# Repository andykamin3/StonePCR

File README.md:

# StonePCR
*Por Joaquín Alonso, Manuel Agustín Gonzalez y Andrés Kaminker*

## Introducción

### ¿Qué es una máquina de PCR?
También conocido como termociclador es un elemento esencial en laboratorios de biología molecular dado que permite realizar, los ciclos térmicos esenciales en la reacción en cadena de la polimerasa. Es por esto que son utilizados en múltiples procesos, uno de ellos es el test de COVID-19. 
Estos equipos pueden llegar a costar entre 2 y 50 mil dólares en nuestro [país](https://www.onelab.com.ar/pcr). Pese a eso existen alternativas libres como [OpenPCR](https://openpcr.org/) que resultan mucho más baratas. Este es un trabajo que busca ofrecer una alternativa similar a OpenPCR pero con mejores prestaciones a nivel técnico. 

## Selección de Componentes

### ARM Cortex M3

Este microcontrolador fue elegido dado que representaba un improvement por sobre el Atmega328 del OpenPCR. A su vez contaba con pines que soportaban los protocolos necesarios tal como I2C y SPI. Por último contaba con pines que soportaban la interfaz casi directa con un puerto USB, elemento altamente deseable para evitar complicaciones en el desarrollo de la interfaz. Por último, el ADC integrado era suficiente para la lectura de los sensores, proporcionando la precisión suficiente. 
- [Datasheet](https://www.st.com/resource/en/datasheet/stm32f102c8.pdf)
- [Guía de Comienzo Rápido](https://www.st.com/resource/en/application_note/cd00164185-getting-started-with-stm32f10xxx-hardware-development-stmicroelectronics.pdf)

### Comunicación con dispositivos externos

#### USB

En primer lugar dispusimos ofrecer comunicación con una computadora mediante USB-B Micro. De esta manera permitíamos el uso del mismo con un conector fácilmente disponible pero que no agregaba las consideraciones de diseño necesarias del estándar USB-C dado que las prestaciones ofrecidas por este(mayor velocidad y _power delivery_ no fueron consideradas necesarias). Esta interfaz tiene como objetivo ofrecer una configuración rápida y fácil desde la aplicación complementaria en el ordenador. 

#### Bluetooth

Aunque la conexión USB era suficiente, decidimos agregar un módulo Bluetooth (HC-05) que permita la conexión inalámbrica a una app _companion_ en un teléfono celular que facilite el trabajo del usuario y le ofrezca recordatorios y alarmas sin tener que estar permanentemente alerta. 

### Sensado de Temperatura

Para el sensado de temperatura decidimos utilizar termistores NTC ofrecidos por Vishay(Modelo: (NTCLE317E4103SBA [https://www.vishay.com/docs/29216/ntcle317e4103sba.pdf]) que tenían las características técnicas necesarias, especialmente la precisión. A través de un divisor resistivo y el ADC del ARM Cortex M3 obtenemos el valor de temperatura, necesario para realizar correctamente los ciclos térmicos. 

### Placas de Peltier y Drivers

Las placas de Peltier seleccionadas, componente esencial del sistema, fueron un componente complejo de seleccionar pero finalmente nos decantamos por [VT-127-1.0-1.3-71](https://tetech.com/wp-content/uploads/2019/03/VT-127-1.0-1.3-71.pdf) de Tetech. La temperatura soportada y la alta potencia que manejan las convirtieron en una opción idónea para el proceso seleccionado. Los drivers fueron seleccionados en función a las placas de Peltier y sus altos requerimientos eléctricos. Es por eso que el driver [VNH5019A](https://www.pololu.com/product/1449) de Pololu fue seleccionadop porque podía entregar la potencia necesaria y era relativamente asequible. 

### Módulo de Pantalla

Para simplificar el desarrollo de la interfaz de usuario y prescindir de una miríada de botones y perillas decidimos usar una pantalla táctil. Para ello fue seleccionado el módulo de Adafruit [ILI9341](https://www.adafruit.com/product/2478). De esta manera disponemos de una pantalla sin incurrir en complejidades extras.

### Alimentación

Debido a la complejidad que presenta la placa y siguiendo los pasos de OpenPCR nos decantamos por el uso de un conector ATX-24 y una fuente externa lo que facilita el routeo y nos provee de líneas de alimentación con poco ruido en 3.3V y 12V.

## Tareas Pendientes 

- [x] Esquemático
- [x] Placement
- Routeo

## Imágenes

- Render del PCB en 3D

## Instrucciones de Uso del Proyecto
- Realizar una descarga o clonar el repositorio de forma local
- Abrir usando KiCad 5.1.6

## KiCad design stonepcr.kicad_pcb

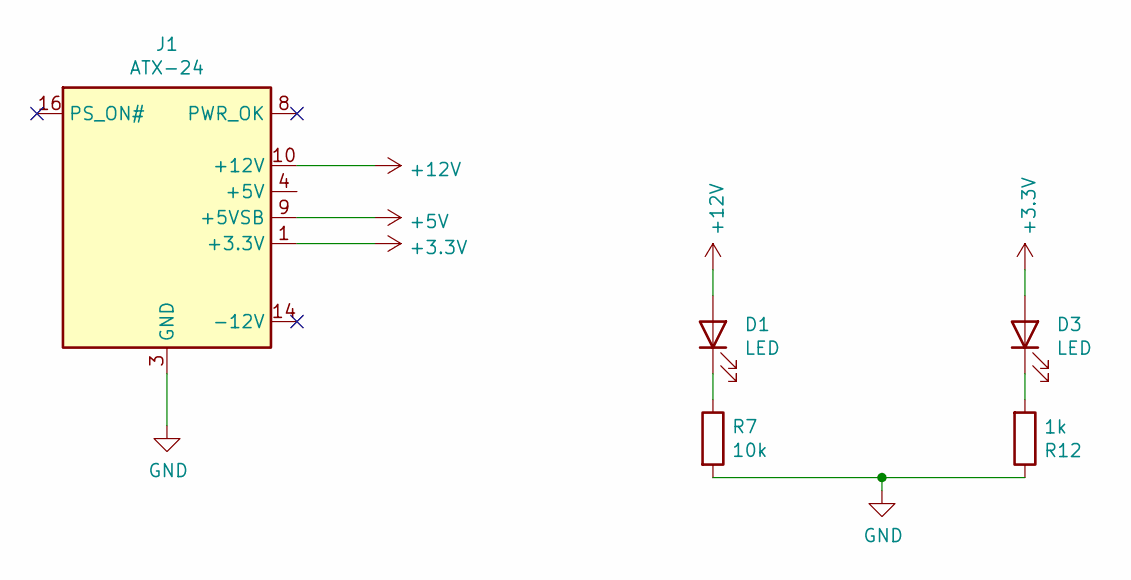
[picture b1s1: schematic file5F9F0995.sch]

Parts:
D1, D3: LED; LED_0805_2012Metric
J1: ATX-24; Molex_Mini-Fit_Jr_5566-24A_2x12_P4.20mm_Vertical
R7: 10k; R_0805_2012Metric
R12: 1k; R_0805_2012Metric

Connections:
+3V3: D3.2 (A), J1.1 (+3.3V), J1.2 (+3.3V), J1.12 (+3.3V), J1.13 (+3.3V); also elsewhere on the board
+5V: J1.9 (+5VSB)
+12V: D1.2 (A), J1.10 (+12V), J1.11 (+12V); also elsewhere on the board
GND: J1.3 (GND), J1.5 (GND), J1.7 (GND), J1.15 (GND), J1.17 (GND), J1.18 (GND), J1.19 (GND), J1.24 (GND), R7.2, R12.1; also elsewhere on the board
unnamed: D1.1 (K), R7.1
unnamed: D3.1 (K), R12.2
unnamed: J1.4 (+5V), J1.6 (+5V), J1.21 (+5V), J1.22 (+5V), J1.23 (+5V)

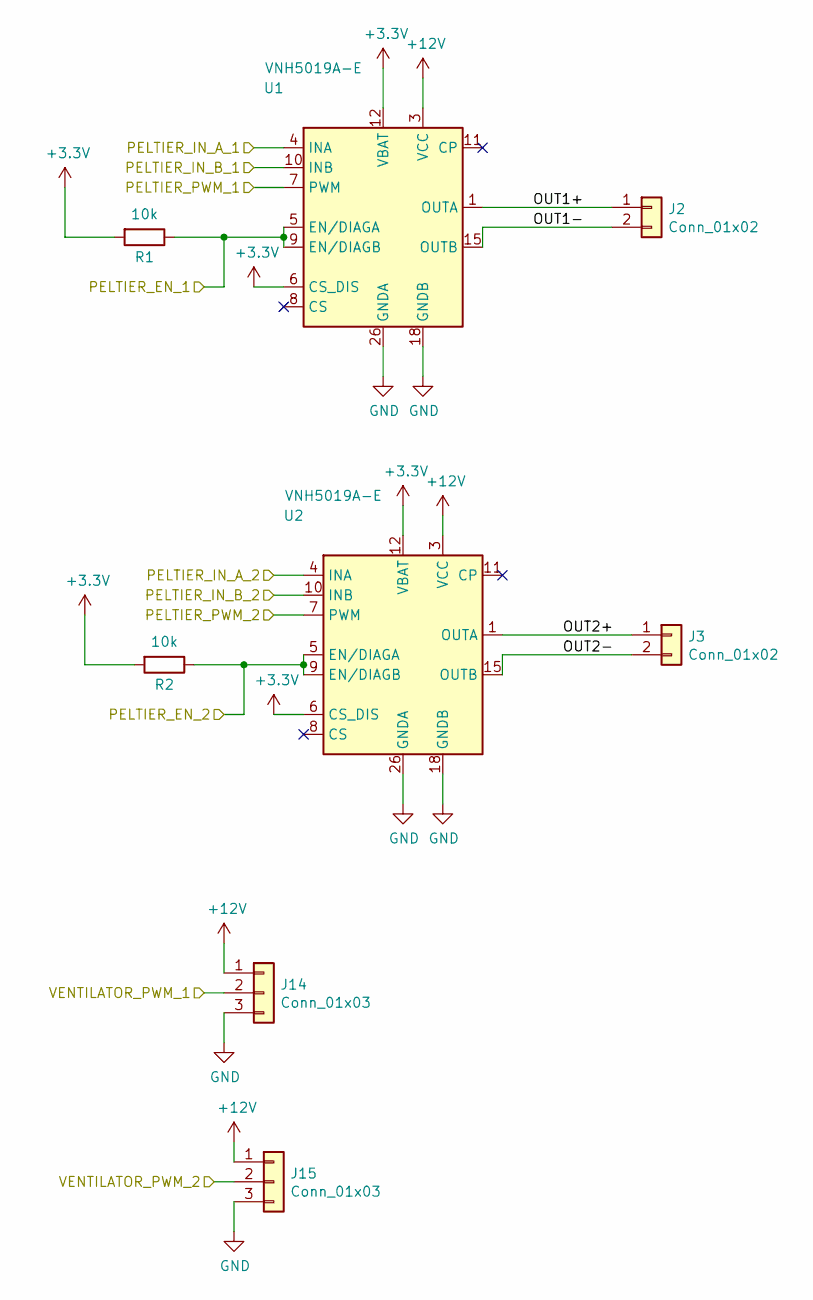
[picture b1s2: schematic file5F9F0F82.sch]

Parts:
J2, J3: Conn_01x02; Molex_Sabre_43160-0102_1x02_P7.49mm_Vertical_ThermalVias
J14, J15: Conn_01x03; PinSocket_1x03_P2.54mm_Vertical
R1, R2: 10k; R_0805_2012Metric
U1, U2: VNH5019A-E; ST_MultiPowerSO-30

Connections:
+3V3: R1.2, R2.2, U1.6 (CS_DIS), U1.12 (VBAT), U2.6 (CS_DIS), U2.12 (VBAT); also elsewhere on the board
+12V: J14.1, J15.1, U1.3 (VCC), U1.13 (VCC), U1.23 (VCC), U1.31 (VCC), U2.3 (VCC), U2.13 (VCC), U2.23 (VCC), U2.31 (VCC); also elsewhere on the board
/ControllerSchematic/PELTIER_EN_1: R1.1, U1.5 (EN/DIAGA), U1.9 (EN/DIAGB); also elsewhere on the board
/ControllerSchematic/PELTIER_EN_2: R2.1, U2.5 (EN/DIAGA), U2.9 (EN/DIAGB); also elsewhere on the board
/ControllerSchematic/PELTIER_IN_A_1: U1.4 (INA); also elsewhere on the board
/ControllerSchematic/PELTIER_IN_A_2: U2.4 (INA); also elsewhere on the board
/ControllerSchematic/PELTIER_IN_B_1: U1.10 (INB); also elsewhere on the board
/ControllerSchematic/PELTIER_IN_B_2: U2.10 (INB); also elsewhere on the board
/ControllerSchematic/PELTIER_PWM_1: U1.7 (PWM); also elsewhere on the board
/ControllerSchematic/PELTIER_PWM_2: U2.7 (PWM); also elsewhere on the board
/ControllerSchematic/VENTILADOR_PWM_1: J15.2; also elsewhere on the board
/ControllerSchematic/VENTILADOR_PWM_2: J14.2; also elsewhere on the board
/PeltierSchematic/OUT1+: J2.1, U1.1 (OUTA), U1.25 (OUTA), U1.30 (OUTA), U1.33 (OUTA)
/PeltierSchematic/OUT1-: J2.2, U1.15 (OUTB), U1.16 (OUTB), U1.21 (OUTB), U1.32 (OUTB)
/PeltierSchematic/OUT2+: J3.1, U2.1 (OUTA), U2.25 (OUTA), U2.30 (OUTA), U2.33 (OUTA)
/PeltierSchematic/OUT2-: J3.2, U2.15 (OUTB), U2.16 (OUTB), U2.21 (OUTB), U2.32 (OUTB)
GND: J14.3, J15.3, U1.18 (GNDB), U1.19 (GNDB), U1.20 (GNDB), U1.26 (GNDA), U1.27 (GNDA), U1.28 (GNDA), U2.18 (GNDB), U2.19 (GNDB), U2.20 (GNDB), U2.26 (GNDA), U2.27 (GNDA), U2.28 (GNDA); also elsewhere on the board

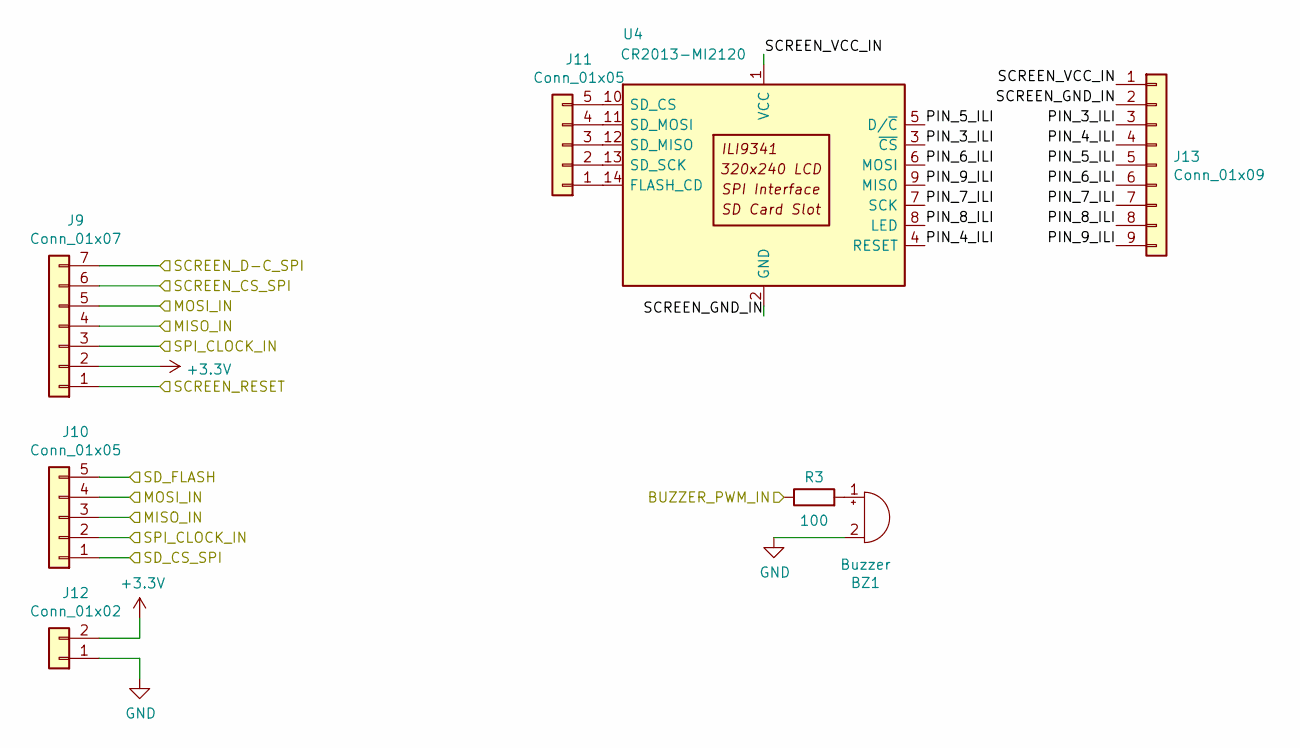
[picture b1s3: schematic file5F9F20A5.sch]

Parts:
BZ1: Buzzer; Buzzer_Mallory_AST1109MLTRQ
J9: Conn_01x07; PinSocket_1x07_P2.54mm_Vertical
J10, J11: Conn_01x05; PinSocket_1x05_P2.54mm_Vertical
J12: Conn_01x02; PinSocket_1x02_P2.54mm_Vertical
J13: Conn_01x09; PinSocket_1x09_P2.54mm_Vertical
R3: 100; R_0805_2012Metric
U4: CR2013-MI2120

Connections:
+3V3: J9.2, J12.2; also elsewhere on the board
/ControllerSchematic/BUZZER_PWM_IN: R3.1; also elsewhere on the board
/ControllerSchematic/SCREEN_CS_SPI: J9.6; also elsewhere on the board
/ControllerSchematic/SCREEN_D-C_SPI: J9.7; also elsewhere on the board
/ControllerSchematic/SCREEN_RESET: J9.1; also elsewhere on the board
/ControllerSchematic/SD_CS_SPI: J10.1; also elsewhere on the board
/ControllerSchematic/SD_FLASH: J10.5; also elsewhere on the board
/ControllerSchematic/SPI_CLOCK_IN: J9.3, J10.2; also elsewhere on the board
/DisplaySchematic/MISO_IN: J9.4, J10.3; also elsewhere on the board
/DisplaySchematic/MOSI_IN: J9.5, J10.4; also elsewhere on the board
/DisplaySchematic/PIN_3_ILI: J13.3, U4.3 (~CS)
/DisplaySchematic/PIN_4_ILI: J13.4, U4.4 (RESET)
/DisplaySchematic/PIN_5_ILI: J13.5, U4.5 (D/~C)
/DisplaySchematic/PIN_6_ILI: J13.6, U4.6 (MOSI)
/DisplaySchematic/PIN_7_ILI: J13.7, U4.7 (SCK)
/DisplaySchematic/PIN_8_ILI: J13.8, U4.8 (LED)
/DisplaySchematic/PIN_9_ILI: J13.9, U4.9 (MISO)
/DisplaySchematic/SCREEN_GND_IN: J13.2, U4.2 (GND)
/DisplaySchematic/SCREEN_VCC_IN: J13.1, U4.1 (VCC)
GND: BZ1.2 (+), J12.1; also elsewhere on the board
unnamed: BZ1.1 (-), R3.2
unnamed: J11.1, U4.14 (FLASH_CD)
unnamed: J11.2, U4.13 (SD_SCK)
unnamed: J11.3, U4.12 (SD_MISO)
unnamed: J11.4, U4.11 (SD_MOSI)
unnamed: J11.5, U4.10 (SD_CS)

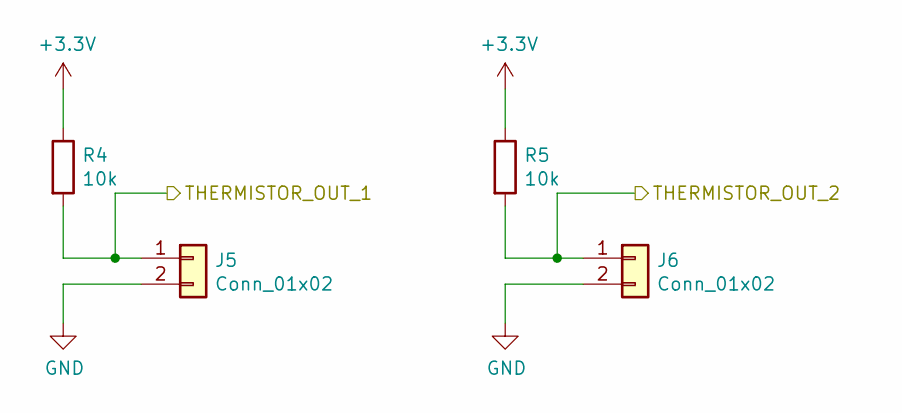
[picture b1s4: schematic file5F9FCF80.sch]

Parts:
J5, J6: Conn_01x02; PinHeader_1x02_P2.54mm_Vertical
R4, R5: 10k; R_0805_2012Metric

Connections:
+3V3: R4.1, R5.1; also elsewhere on the board
/ControllerSchematic/THERMISTOR_IN_1: J5.1, R4.2; also elsewhere on the board
/ControllerSchematic/THERMISTOR_IN_2: J6.1, R5.2; also elsewhere on the board
GND: J5.2, J6.2; also elsewhere on the board

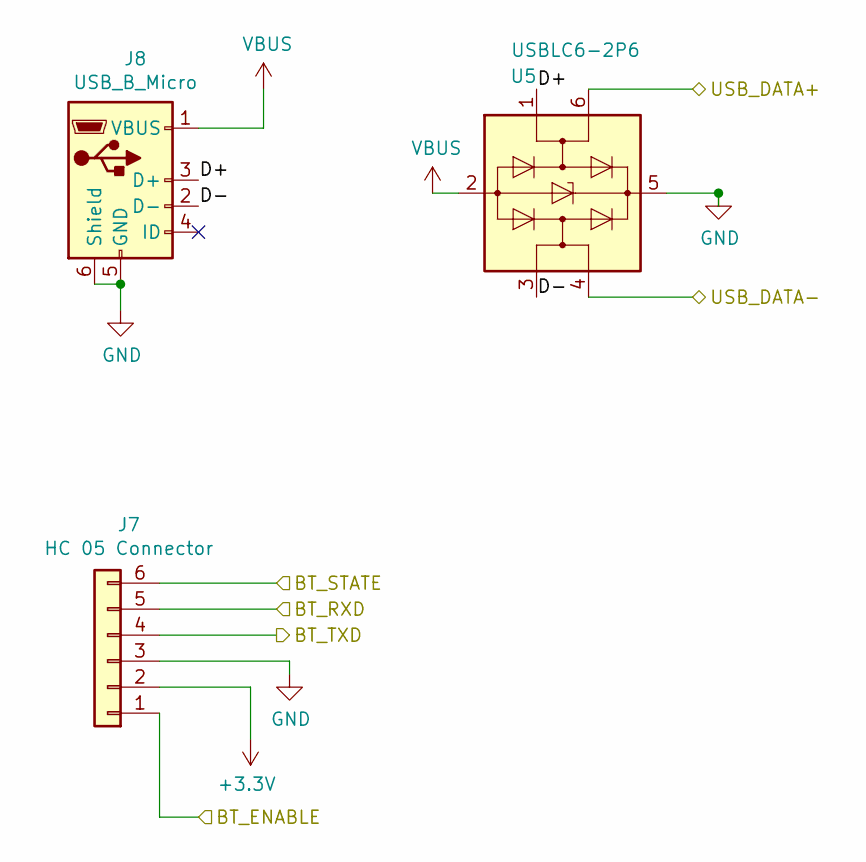
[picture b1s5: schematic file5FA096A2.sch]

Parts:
J7: HC 05 Connector; PinHeader_1x06_P2.54mm_Vertical
J8: USB_B_Micro; USB_Micro-B_Wuerth_629105150521
U5: USBLC6-2P6; SOT-666

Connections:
+3V3: J7.2; also elsewhere on the board
/ControllerSchematic/BT_ENABLE: J7.1; also elsewhere on the board
/ControllerSchematic/BT_RXD: J7.5; also elsewhere on the board
/ControllerSchematic/BT_STATE: J7.6; also elsewhere on the board
/ControllerSchematic/BT_TXD: J7.4; also elsewhere on the board
/ControllerSchematic/USB_DATA+: U5.6 (I/O1); also elsewhere on the board
/ControllerSchematic/USB_DATA-: U5.4 (I/O2); also elsewhere on the board
/InterfacesSchematic/D+: J8.3 (D+), U5.1 (I/O1)
/InterfacesSchematic/D-: J8.2 (D-), U5.3 (I/O2)
GND: J7.3, J8.5 (GND), J8.6 (Shield), U5.5 (VBUS); also elsewhere on the board
VBUS: J8.1 (VBUS), U5.2 (GND)

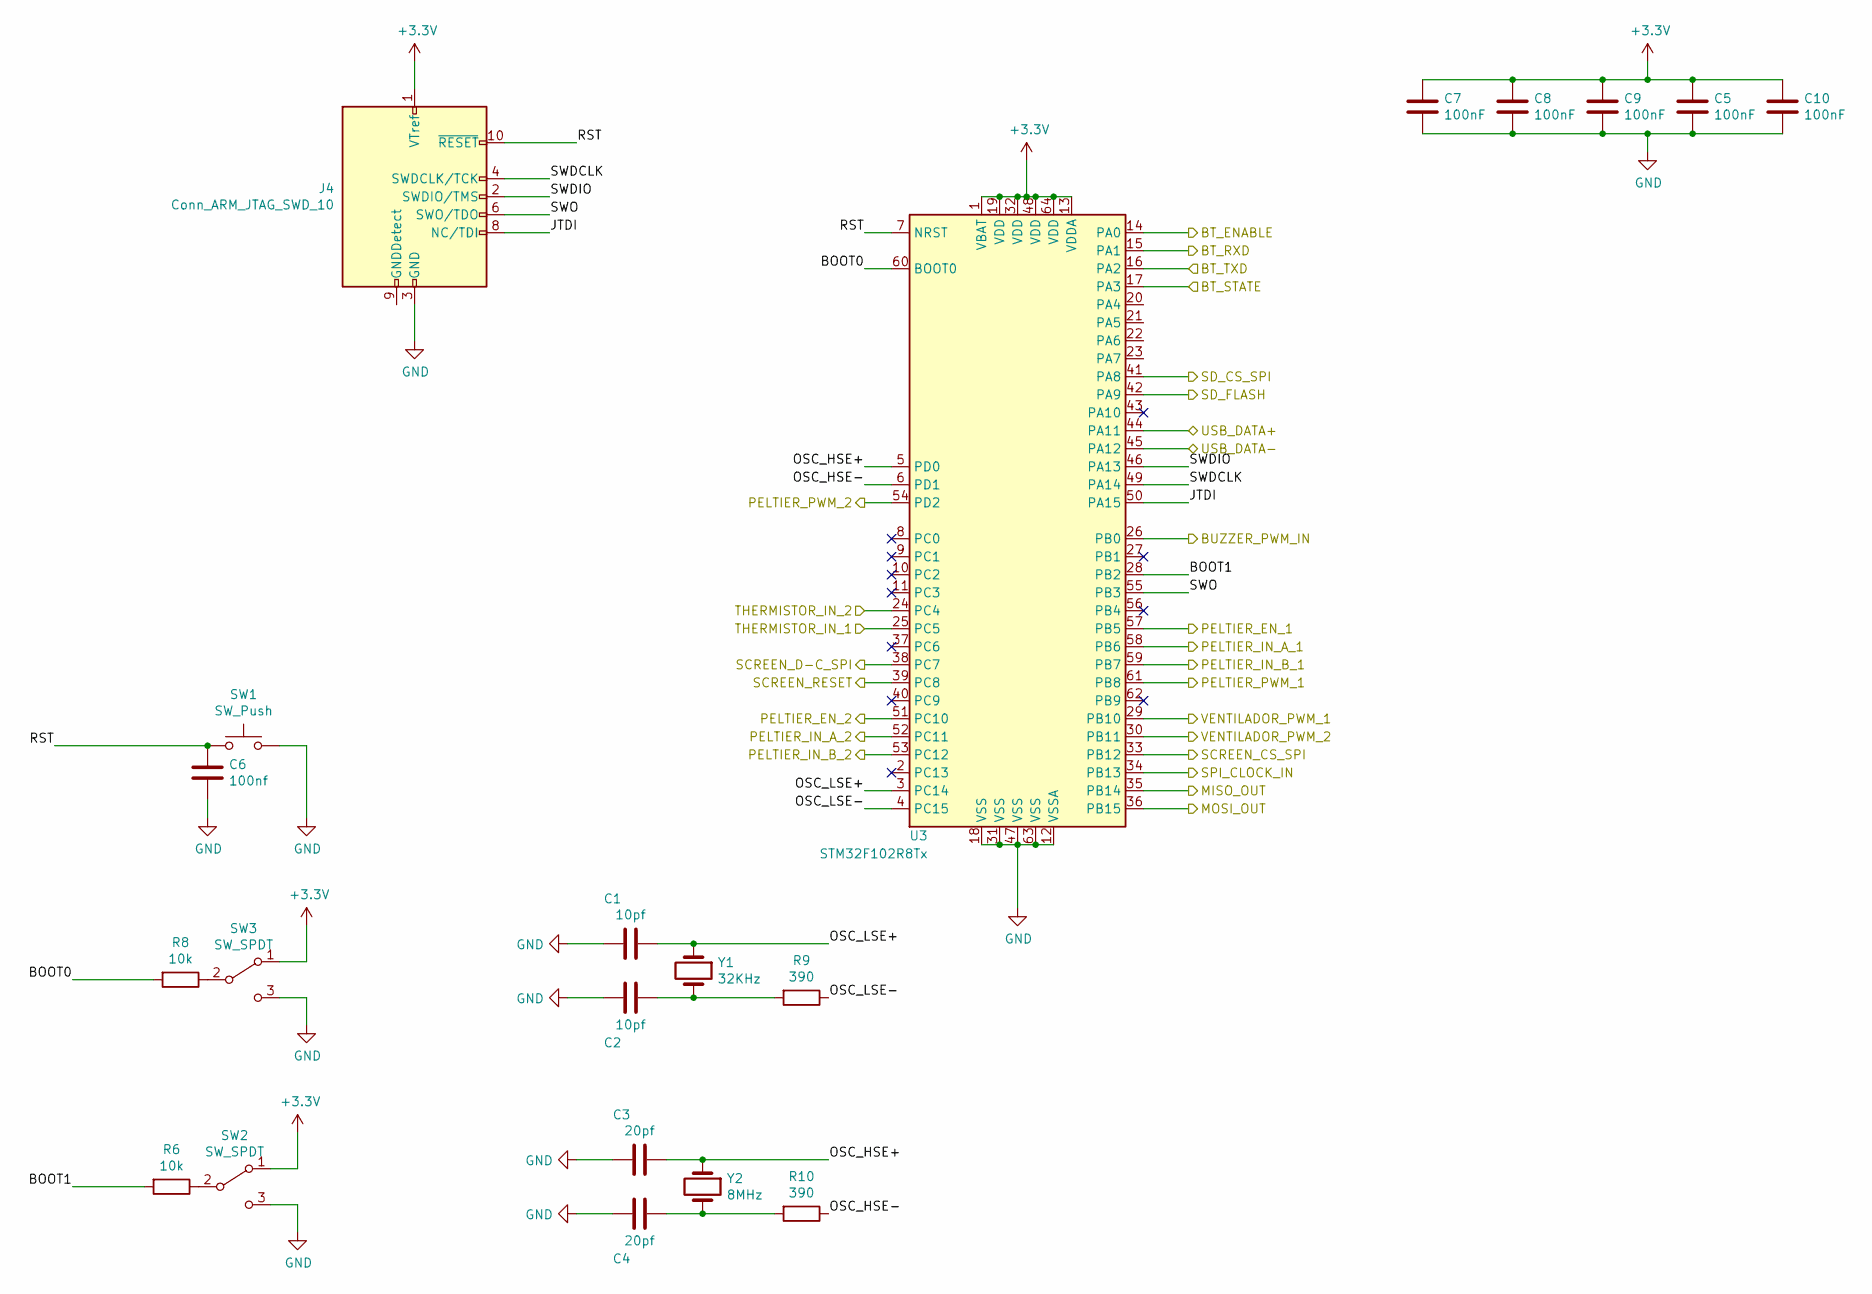
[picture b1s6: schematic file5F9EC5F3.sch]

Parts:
C1, C2: 10pf; C_0805_2012Metric
C3, C4: 20pf; C_0805_2012Metric
C5, C7, C8, C9, C10: 100nF; C_0805_2012Metric
C6: 100nf; C_0805_2012Metric
J4: Conn_ARM_JTAG_SWD_10; JST_EH_B10B-EH-A_1x10_P2.50mm_Vertical
R6, R8: 10k; R_0805_2012Metric
R9, R10: 390; R_0805_2012Metric
SW1: SW_Push; SW_SPST_CK_RS282G05A3
SW2, SW3: SW_SPDT; SW_SPDT_PCM12
U3: STM32F102R8Tx; LQFP-64_10x10mm_P0.5mm
Y1: 32KHz; Resonator-2Pin_W7.0mm_H2.5mm
Y2: 8MHz; Resonator-2Pin_W7.0mm_H2.5mm

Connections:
+3V3: C5.1, C7.1, C8.1, C9.1, C10.1, J4.1 (VTref), SW2.1 (A), SW3.1 (A), U3.1 (VBAT), U3.13 (VDDA), U3.19 (VDD), U3.32 (VDD), U3.48 (VDD), U3.64 (VDD); also elsewhere on the board
/ControllerSchematic/BOOT0: R8.2, U3.60 (BOOT0)
/ControllerSchematic/BOOT1: R6.2, U3.28 (PB2)
/ControllerSchematic/BT_ENABLE: U3.14 (PA0); also elsewhere on the board
/ControllerSchematic/BT_RXD: U3.15 (PA1); also elsewhere on the board
/ControllerSchematic/BT_STATE: U3.17 (PA3); also elsewhere on the board
/ControllerSchematic/BT_TXD: U3.16 (PA2); also elsewhere on the board
/ControllerSchematic/BUZZER_PWM_IN: U3.26 (PB0); also elsewhere on the board
/ControllerSchematic/JTDI: J4.8 (NC/TDI), U3.50 (PA15)
/ControllerSchematic/OSC_HSE+: C3.1, U3.5 (PD0), Y2.1
/ControllerSchematic/OSC_HSE-: R10.1, U3.6 (PD1)
/ControllerSchematic/OSC_LSE+: C1.1, U3.3 (PC14), Y1.1
/ControllerSchematic/OSC_LSE-: R9.1, U3.4 (PC15)
/ControllerSchematic/PELTIER_EN_1: U3.57 (PB5); also elsewhere on the board
/ControllerSchematic/PELTIER_EN_2: U3.51 (PC10); also elsewhere on the board
/ControllerSchematic/PELTIER_IN_A_1: U3.58 (PB6); also elsewhere on the board
/ControllerSchematic/PELTIER_IN_A_2: U3.52 (PC11); also elsewhere on the board
/ControllerSchematic/PELTIER_IN_B_1: U3.59 (PB7); also elsewhere on the board
/ControllerSchematic/PELTIER_IN_B_2: U3.53 (PC12); also elsewhere on the board
/ControllerSchematic/PELTIER_PWM_1: U3.61 (PB8); also elsewhere on the board
/ControllerSchematic/PELTIER_PWM_2: U3.54 (PD2); also elsewhere on the board
/ControllerSchematic/RST: C6.1, J4.10 (~RESET~), SW1.1, U3.7 (NRST)
/ControllerSchematic/SCREEN_CS_SPI: U3.33 (PB12); also elsewhere on the board
/ControllerSchematic/SCREEN_D-C_SPI: U3.38 (PC7); also elsewhere on the board
/ControllerSchematic/SCREEN_RESET: U3.39 (PC8); also elsewhere on the board
/ControllerSchematic/SD_CS_SPI: U3.41 (PA8); also elsewhere on the board
/ControllerSchematic/SD_FLASH: U3.42 (PA9); also elsewhere on the board
/ControllerSchematic/SPI_CLOCK_IN: U3.34 (PB13); also elsewhere on the board
/ControllerSchematic/SWDCLK: J4.4 (SWDCLK/TCK), U3.49 (PA14)
/ControllerSchematic/SWDIO: J4.2 (SWDIO/TMS), U3.46 (PA13)
/ControllerSchematic/SWO: J4.6 (SWO/TDO), U3.55 (PB3)
/ControllerSchematic/THERMISTOR_IN_1: U3.25 (PC5); also elsewhere on the board
/ControllerSchematic/THERMISTOR_IN_2: U3.24 (PC4); also elsewhere on the board
/ControllerSchematic/USB_DATA+: U3.44 (PA11); also elsewhere on the board
/ControllerSchematic/USB_DATA-: U3.45 (PA12); also elsewhere on the board
/ControllerSchematic/VENTILADOR_PWM_1: U3.29 (PB10); also elsewhere on the board
/ControllerSchematic/VENTILADOR_PWM_2: U3.30 (PB11); also elsewhere on the board
/DisplaySchematic/MISO_IN: U3.35 (PB14); also elsewhere on the board
/DisplaySchematic/MOSI_IN: U3.36 (PB15); also elsewhere on the board
GND: C1.2, C2.2, C3.2, C4.2, C5.2, C6.2, C7.2, C8.2, C9.2, C10.2, J4.3 (GND), J4.5 (GND), SW1.2, SW2.3 (C), SW3.3 (C), U3.12 (VSSA), U3.18 (VSS), U3.31 (VSS), U3.47 (VSS), U3.63 (VSS); also elsewhere on the board
unnamed: C2.1, R9.2, Y1.2
unnamed: C4.1, R10.2, Y2.2
unnamed: R6.1, SW2.2 (B)
unnamed: R8.1, SW3.2 (B)

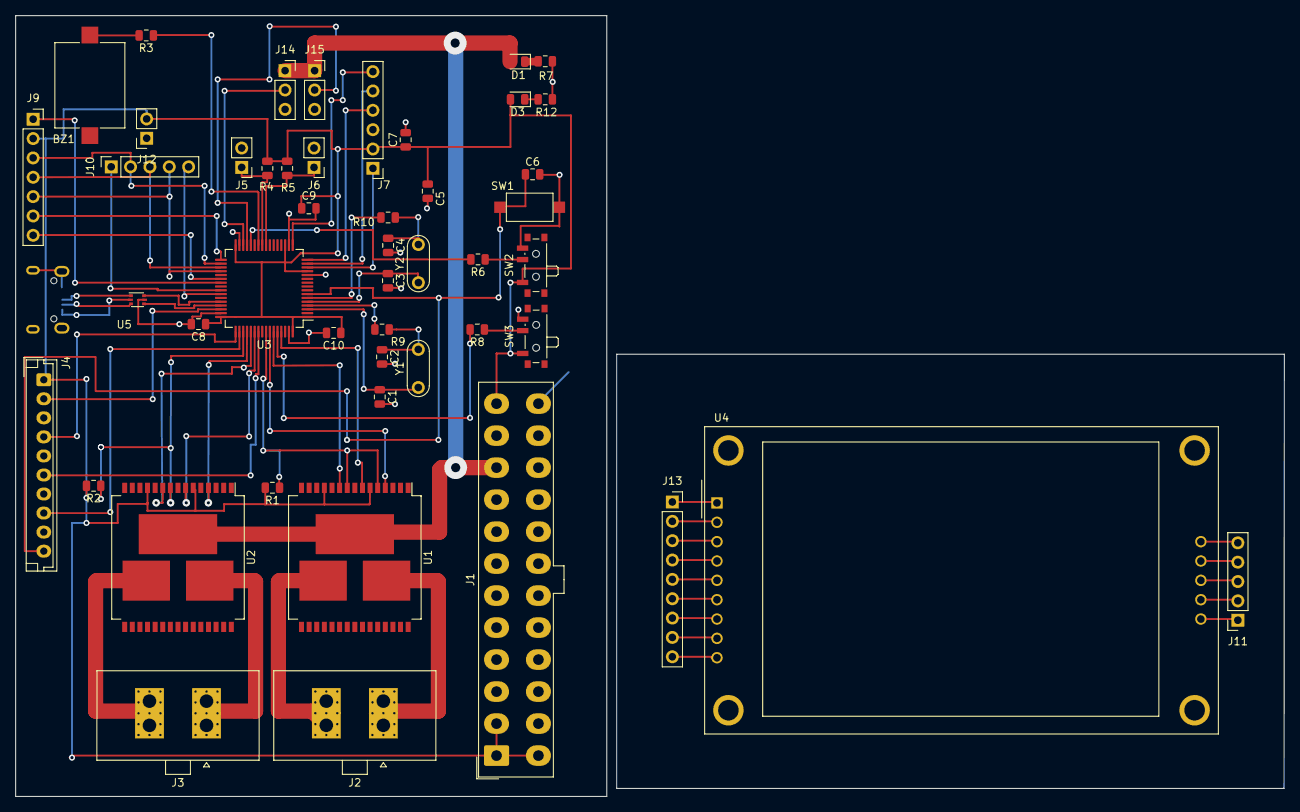
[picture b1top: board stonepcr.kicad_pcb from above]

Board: 2 copper layers, 166.6 x 102.5 mm, 49 parts (1 on the bottom side), 70 nets.

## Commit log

2020-11-01 Initial commit
    :)
2020-11-01 Cosas
    - Power
    - I/O
    - Screen
    - Sensing
2020-11-04 Finished schematic
2020-11-04 Added footprints
2020-11-15 Placement
2020-11-15 Caches y autosaves
2020-11-16 Preparation for differential routing and small placement corrections.
2020-11-16 Update fp-info-cache
2020-11-17 Trackeo
    Pobre trackeo parcial. Backup
2020-11-17 Replacement and adjustments
2020-11-17 Adjustments
2020-11-17 Rotación Swithc
2020-11-19 Initial Routing
2020-11-19 Removal of LED 5V and further routing
2020-11-20 Copper layer for logic
